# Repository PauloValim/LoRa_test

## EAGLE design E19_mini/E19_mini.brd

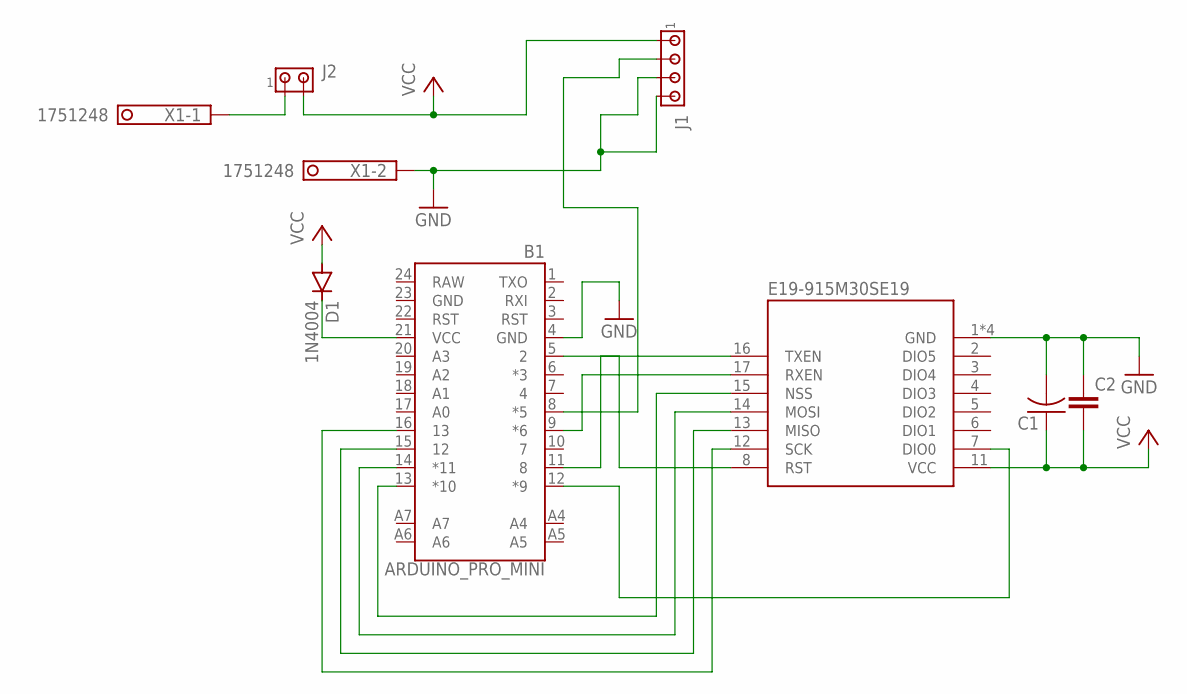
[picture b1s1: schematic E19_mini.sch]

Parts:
B1: ARDUINO_PRO_MINI
C1: C-US050-024X044; C050-024X044
C2: C-EU025-024X044; C025-024X044
D1: 1N4004; DO41-10
J1: MTA04-100; 10X04MTA
J2: MTA02-100; 10X02MTA
U1: E19-915M30SE19; DIP2540W53P254L2400H508Q18B
X1: 1751248

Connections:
GND: B1.4 (GND), B1.23 (GND), C1.2, C2.1, J1.3, J1.4, U1.1 (GND), U1.9 (GND), U1.10 (GND), U1.18 (GND), X1.2
unnamed: B1.5 (2), U1.8 (RST)
unnamed: B1.16 (13), U1.12 (SCK)
unnamed: B1.15 (12), U1.13 (MISO)
unnamed: B1.14 (*11), U1.14 (MOSI)
unnamed: B1.13 (*10), U1.15 (NSS)
unnamed: B1.11 (8), U1.16 (TXEN)
unnamed: B1.9 (*6), U1.17 (RXEN)
unnamed: B1.21 (VCC), D1.C
unnamed: J2.1, X1.1
unnamed: B1.12 (*9), U1.7 (DIO0)
unnamed: B1.8 (*5), J1.2
RAW: B1.24 (RAW)
VCC: C1.1, C2.2, D1.A, J1.1, J2.2, U1.11 (VCC)

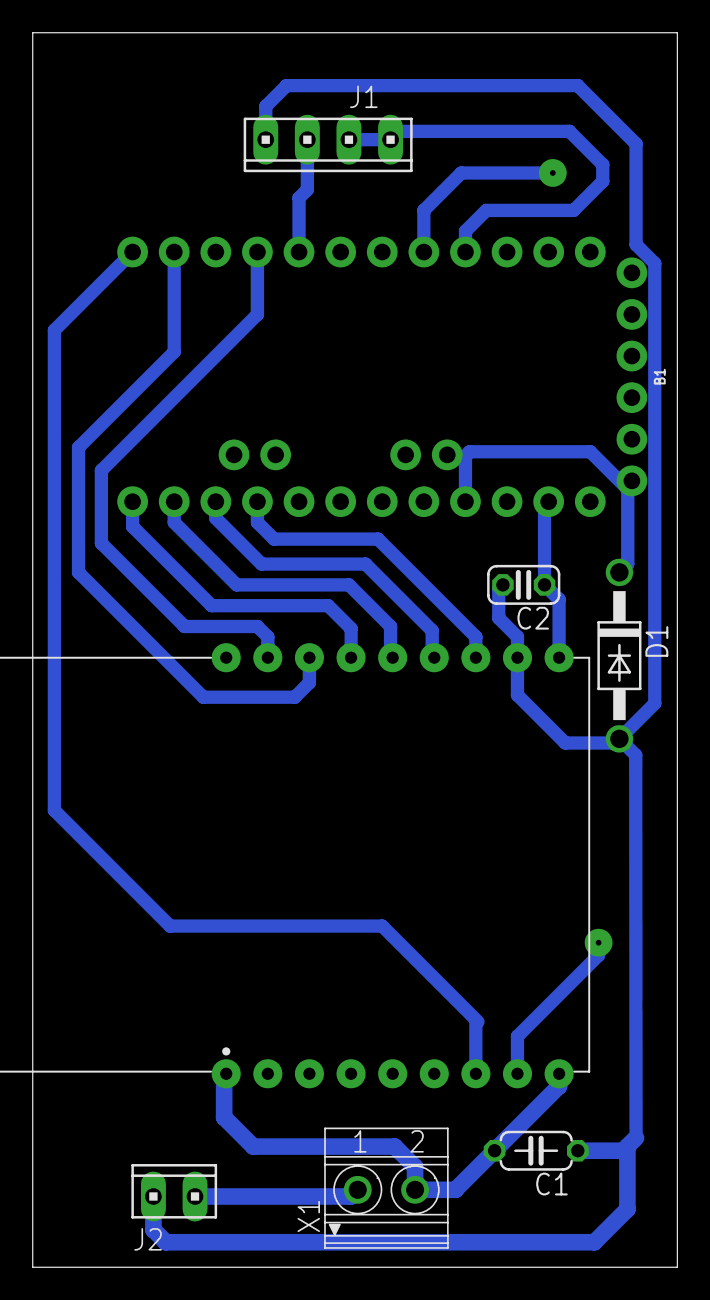
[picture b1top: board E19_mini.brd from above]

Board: 2 copper layers, 39.4 x 75.4 mm, 8 parts (0 on the bottom side), 13 nets.

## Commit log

2020-01-30 importacao inicial
